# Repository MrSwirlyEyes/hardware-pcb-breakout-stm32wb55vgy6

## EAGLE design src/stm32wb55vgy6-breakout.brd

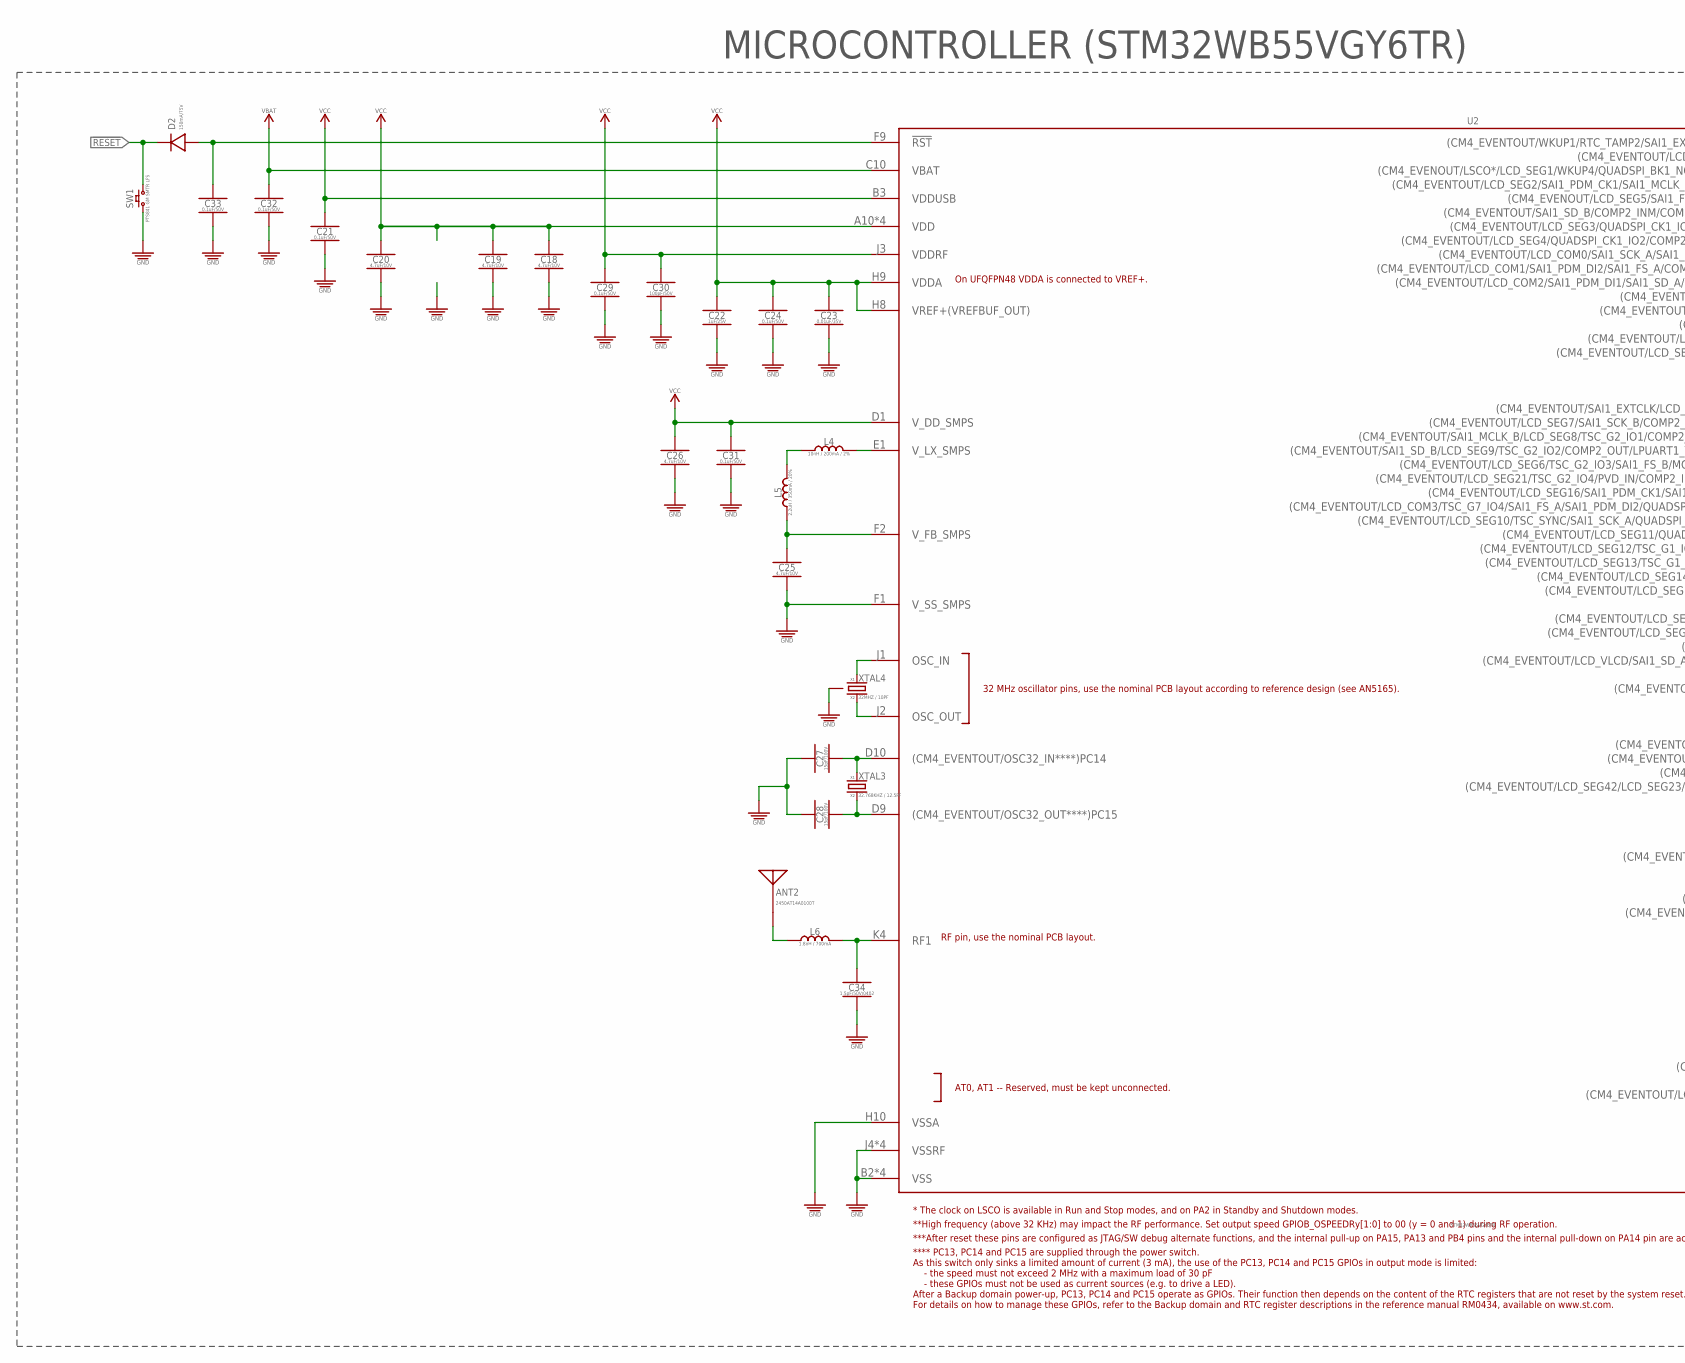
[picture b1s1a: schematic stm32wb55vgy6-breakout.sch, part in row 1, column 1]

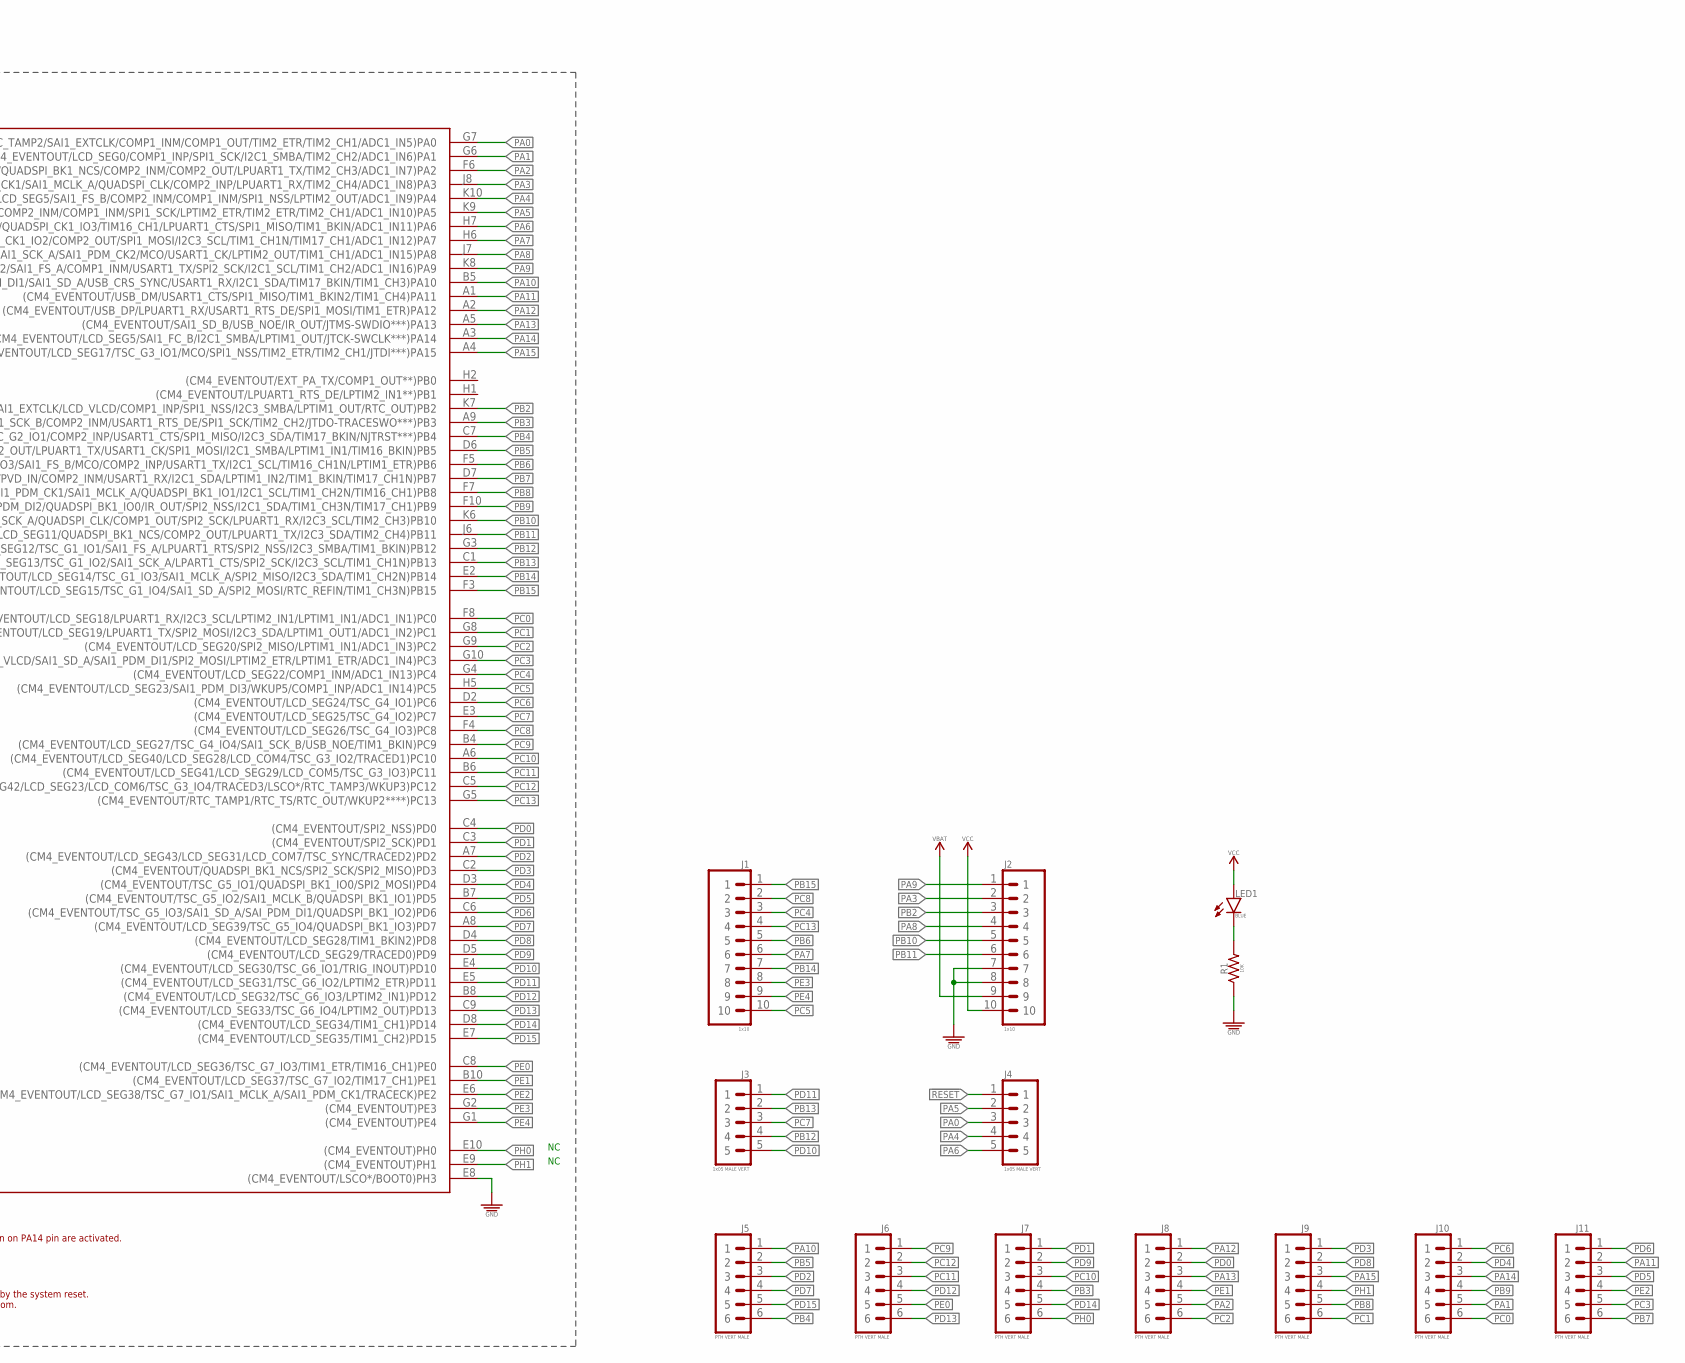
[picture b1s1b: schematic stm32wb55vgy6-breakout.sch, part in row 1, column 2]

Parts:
ANT2: 2450AT14A0100T; RESC1608X40N
C18, C19, C20, C25, C26: 4.7uF/10V; CAPC1005X55_SMD-0402
C21, C24, C29, C31, C32, C33: 0.1uF/50V; CAPC1005X55_SMD-0402
C22: 1uF/25V; CAPC1005X55_SMD-0402
C23: 0.01uF/35V; CAPC1005X55_SMD-0402
C27, C28: 15pF/100V; CAPC1005X55_SMD-0402
C30: 100pF/50V; CAPC1005X55_SMD-0402
C34: 1.5pF/50V/0402; CAPC1005X55_SMD-0402
D2: 150mA/75V; DFN100X60X55-2
J1, J2: 1x10; HDRV10W64P254_1X10_2540X254X838B
J3, J4: 1x05 MALE VERT; HDRV5W64P254_1X5_1270X254X838B
J5, J6, J7, J8, J9, J10, J11: PTH VERT MALE; HDRV6W64P254_1X6_1524X254X838B
L4: 10nH / 200mA / 2%; INDC1005X32N
L5: 2.2uH / 350mA / 20%; INDC1005X32N
L6: 1.8nH / 700mA; INDC1005X32N
LED1: BLUE; LEDC1005X40_LED-0402
R1: 10K; RESC1005X35_SMD-0402
SW1: PTS841 GM SMTR LFS; SW_MOMENTARY_SPST-NO_PTS841-GM-SMTR-LFS
U2: STM32WB55VGY6TR; BGA100N40P10X10_438X440X59N
XTAL3: 32.768KHZ / 12.5PF; OSCCC205X120X55N
XTAL4: 32MHZ / 10PF; OSCCC200X160X59N

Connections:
!RESET!: D2.K, J4.1, SW1.3 (2), SW1.4 (2)
FEED: ANT2.FEED, L6.1
GND: C18.2, C19.2, C20.2, C21.2, C22.2, C23.2, C24.2, C25.2, C26.2, C27.1, C28.1, C29.2, C30.2, C31.2, C32.2, C33.2, C34.2, J2.7, J2.8, R1.1, SW1.1, SW1.2 (1), U2.B2 (VSS), U2.B9 (VSS), U2.E8 ((CM4_EVENTOUT/LSCO*/BOOT0)PH3), U2.F1 (V_SS_SMPS), U2.H10 (VSSA), U2.J4 (VSSRF), U2.J5 (VSS), U2.J9 (VSS), U2.K1 (VSSRF), U2.K2 (VSSRF), U2.K3 (VSSRF), XTAL4.2 (GND), XTAL4.4 (GND)
unnamed: LED1.K, R1.2
unnamed: L4.1, L5.2
unnamed: C25.1, L5.1, U2.F2 (V_FB_SMPS)
unnamed: U2.J1 (OSC_IN), XTAL4.1 (XTAL1)
unnamed: U2.J2 (OSC_OUT), XTAL4.3 (XTAL2)
unnamed: C27.2, U2.D10 ((CM4_EVENTOUT/OSC32_IN****)PC14), XTAL3.X1
unnamed: C28.2, U2.D9 ((CM4_EVENTOUT/OSC32_OUT****)PC15), XTAL3.X2
unnamed: L4.2, U2.E1 (V_LX_SMPS)
unnamed: C33.1, D2.A, U2.F9 (!RST!)
PA0: J4.3, U2.G7 ((CM4_EVENTOUT/WKUP1/RTC_TAMP2/SAI1_EXTC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)
PA1: J10.5, U2.G6 ((CM4_EVENTOUT/LCD_SEG0/COMP1_INP/SPI1_S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)
PA2: J8.5, U2.F6 ((CM4_EVENOUT/LSCO*/LCD_SEG1/WKUP4/QUADS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)
PA3: J2.2, U2.J8 ((CM4_EVENTOUT/LCD_SEG2/SAI1_PDM_CK1/SAI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)
PA4: J4.4, U2.K10 ((CM4_EVENOUT/LCD_SEG5/SAI1_FS_B/COMP2_I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)
PA5: J4.2, U2.K9 ((CM4_EVENTOUT/SAI1_SD_B/COMP2_INM/COMP1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)
PA6: J4.5, U2.H7 ((CM4_EVENTOUT/LCD_SEG3/QUADSPI_CK1_IO3/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)
PA7: J1.6, U2.H6 ((CM4_EVENTOUT/LCD_SEG4/QUADSPI_CK1_IO2/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)
PA8: J2.4, U2.J7 ((CM4_EVENTOUT/LCD_COM0/SAI1_SCK_A/SAI1_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)
PA9: J2.1, U2.K8 ((CM4_EVENTOUT/LCD_COM1/SAI1_PDM_DI2/SAI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)
PA10: J5.1, U2.B5 ((CM4_EVENTOUT/LCD_COM2/SAI1_PDM_DI1/SAI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)
PA11: J11.2, U2.A1 ((CM4_EVENTOUT/USB_DM/USART1_CTS/SPI1_MI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)
PA12: J8.1, U2.A2 ((CM4_EVENTOUT/USB_DP/LPUART1_RX/USART1_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)
PA13: J8.3, U2.A5 ((CM4_EVENTOUT/SAI1_SD_B/USB_NOE/IR_OUT/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)
PA14: J10.3, U2.A3 ((CM4_EVENTOUT/LCD_SEG5/SAI1_FC_B/I2C1_S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)
PA15: J9.3, U2.A4 ((CM4_EVENTOUT/LCD_SEG17/TSC_G3_IO1/MCO/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)
PB2: J2.3, U2.K7 ((CM4_EVENTOUT/SAI1_EXTCLK/LCD_VLCD/COMP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)
PB3: J7.4, U2.A9 ((CM4_EVENTOUT/LCD_SEG7/SAI1_SCK_B/COMP2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)
PB4: J5.6, U2.C7 ((CM4_EVENTOUT/SAI1_MCLK_B/LCD_SEG8/TSC_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)
PB5: J5.2, U2.D6 ((CM4_EVENTOUT/SAI1_SD_B/LCD_SEG9/TSC_G2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)
PB6: J1.5, U2.F5 ((CM4_EVENTOUT/LCD_SEG6/TSC_G2_IO3/SAI1_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)
PB7: J11.6, U2.D7 ((CM4_EVENTOUT/LCD_SEG21/TSC_G2_IO4/PVD_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)
PB8: J9.5, U2.F7 ((CM4_EVENTOUT/LCD_SEG16/SAI1_PDM_CK1/SA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)
PB9: J10.4, U2.F10 ((CM4_EVENTOUT/LCD_COM3/TSC_G7_IO4/SAI1_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)
PB10: J2.5, U2.K6 ((CM4_EVENTOUT/LCD_SEG10/TSC_SYNC/SAI1_S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)
PB11: J2.6, U2.J6 ((CM4_EVENTOUT/LCD_SEG11/QUADSPI_BK1_NCS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)
PB12: J3.4, U2.G3 ((CM4_EVENTOUT/LCD_SEG12/TSC_G1_IO1/SAI1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)
PB13: J3.2, U2.C1 ((CM4_EVENTOUT/LCD_SEG13/TSC_G1_IO2/SAI1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)
PB14: J1.7, U2.E2 ((CM4_EVENTOUT/LCD_SEG14/TSC_G1_IO3/SAI1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)
PB15: J1.1, U2.F3 ((CM4_EVENTOUT/LCD_SEG15/TSC_G1_IO4/SAI1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)
PC0: J10.6, U2.F8 ((CM4_EVENTOUT/LCD_SEG18/LPUART1_RX/I2C3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)
PC1: J9.6, U2.G8 ((CM4_EVENTOUT/LCD_SEG19/LPUART1_TX/SPI2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)
PC2: J8.6, U2.G9 ((CM4_EVENTOUT/LCD_SEG20/SPI2_MISO/LPTIM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)
PC3: J11.5, U2.G10 ((CM4_EVENTOUT/LCD_VLCD/SAI1_SD_A/SAI1_P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)
PC4: J1.3, U2.G4 ((CM4_EVENTOUT/LCD_SEG22/COMP1_INM/ADC1_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)
PC5: J1.10, U2.H5 ((CM4_EVENTOUT/LCD_SEG23/SAI1_PDM_DI3/WK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)
PC6: J10.1, U2.D2 ((CM4_EVENTOUT/LCD_SEG24/TSC_G4_IO1)PC6)
PC7: J3.3, U2.E3 ((CM4_EVENTOUT/LCD_SEG25/TSC_G4_IO2)PC7)
PC8: J1.2, U2.F4 ((CM4_EVENTOUT/LCD_SEG26/TSC_G4_IO3)PC8)
PC9: J6.1, U2.B4 ((CM4_EVENTOUT/LCD_SEG27/TSC_G4_IO4/SAI1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)
PC10: J7.3, U2.A6 ((CM4_EVENTOUT/LCD_SEG40/LCD_SEG28/LCD_C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)
PC11: J6.3, U2.B6 ((CM4_EVENTOUT/LCD_SEG41/LCD_SEG29/LCD_C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)
PC12: J6.2, U2.C5 ((CM4_EVENTOUT/LCD_SEG42/LCD_SEG23/LCD_C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)
PC13: J1.4, U2.G5 ((CM4_EVENTOUT/RTC_TAMP1/RTC_TS/RTC_OUT/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)
PD0: J8.2, U2.C4 ((CM4_EVENTOUT/SPI2_NSS)PD0)
PD1: J7.1, U2.C3 ((CM4_EVENTOUT/SPI2_SCK)PD1)
PD2: J5.3, U2.A7 ((CM4_EVENTOUT/LCD_SEG43/LCD_SEG31/LCD_C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)
PD3: J9.1, U2.C2 ((CM4_EVENTOUT/QUADSPI_BK1_NCS/SPI2_SCK/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)
PD4: J10.2, U2.D3 ((CM4_EVENTOUT/TSC_G5_IO1/QUADSPI_BK1_IO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)
PD5: J11.3, U2.B7 ((CM4_EVENTOUT/TSC_G5_IO2/SAI1_MCLK_B/QU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)
PD6: J11.1, U2.C6 ((CM4_EVENTOUT/TSC_G5_IO3/SAI1_SD_A/SAI_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)
PD7: J5.4, U2.A8 ((CM4_EVENTOUT/LCD_SEG39/TSC_G5_IO4/QUAD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)
PD8: J9.2, U2.D4 ((CM4_EVENTOUT/LCD_SEG28/TIM1_BKIN2)PD8)
PD9: J7.2, U2.D5 ((CM4_EVENTOUT/LCD_SEG29/TRACED0)PD9)
PD10: J3.5, U2.E4 ((CM4_EVENTOUT/LCD_SEG30/TSC_G6_IO1/TRIG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)
PD11: J3.1, U2.E5 ((CM4_EVENTOUT/LCD_SEG31/TSC_G6_IO2/LPTI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)
PD12: J6.4, U2.B8 ((CM4_EVENTOUT/LCD_SEG32/TSC_G6_IO3/LPTI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)
PD13: J6.6, U2.C9 ((CM4_EVENTOUT/LCD_SEG33/TSC_G6_IO4/LPTI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)
PD14: J7.5, U2.D8 ((CM4_EVENTOUT/LCD_SEG34/TIM1_CH1)PD14)
PD15: J5.5, U2.E7 ((CM4_EVENTOUT/LCD_SEG35/TIM1_CH2)PD15)
PE0: J6.5, U2.C8 ((CM4_EVENTOUT/LCD_SEG36/TSC_G7_IO3/TIM1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)
PE1: J8.4, U2.B10 ((CM4_EVENTOUT/LCD_SEG37/TSC_G7_IO2/TIM1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)
PE2: J11.4, U2.E6 ((CM4_EVENTOUT/LCD_SEG38/TSC_G7_IO1/SAI1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)
PE3: J1.8, U2.G2 ((CM4_EVENTOUT)PE3)
PE4: J1.9, U2.G1 ((CM4_EVENTOUT)PE4)
PH0: J7.6, U2.E10 ((CM4_EVENTOUT)PH0)
PH1: J9.4, U2.E9 ((CM4_EVENTOUT)PH1)
RF: C34.1, L6.2, U2.K4 (RF1)
VBAT: C32.1, J2.9, U2.C10 (VBAT)
VCC: C18.1, C19.1, C20.1, C21.1, C22.1, C23.1, C24.1, C26.1, C29.1, C30.1, C31.1, J2.10, LED1.A, U2.A10 (VDD), U2.B1 (VDD), U2.B3 (VDDUSB), U2.D1 (V_DD_SMPS), U2.H8 (VREF+(VREFBUF_OUT)), U2.H9 (VDDA), U2.J3 (VDDRF), U2.J10 (VDD), U2.K5 (VDD)

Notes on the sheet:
MICROCONTROLLER (STM32WB55VGY6TR)

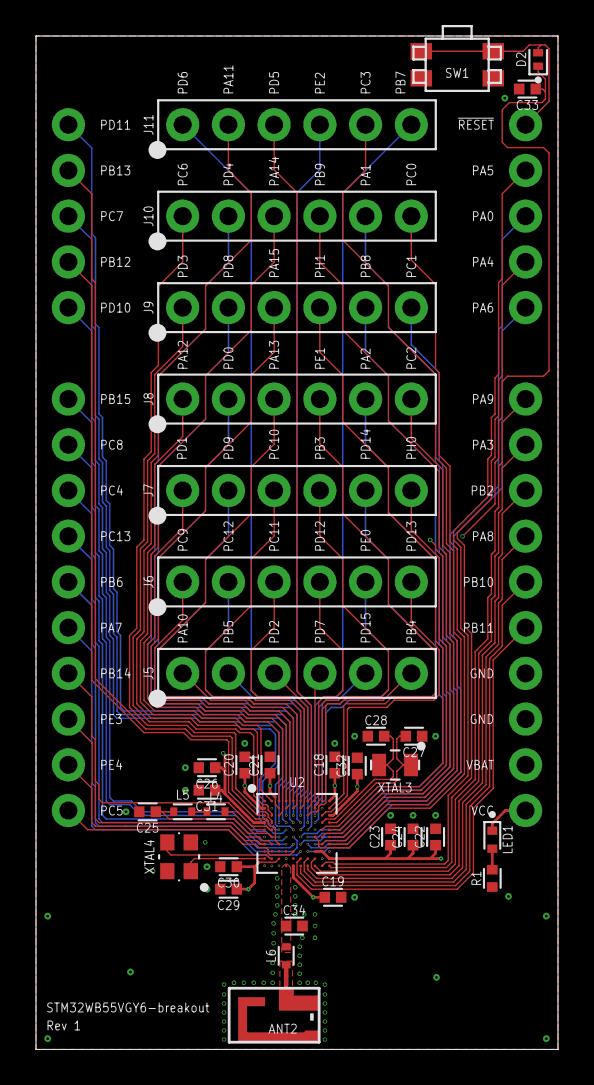
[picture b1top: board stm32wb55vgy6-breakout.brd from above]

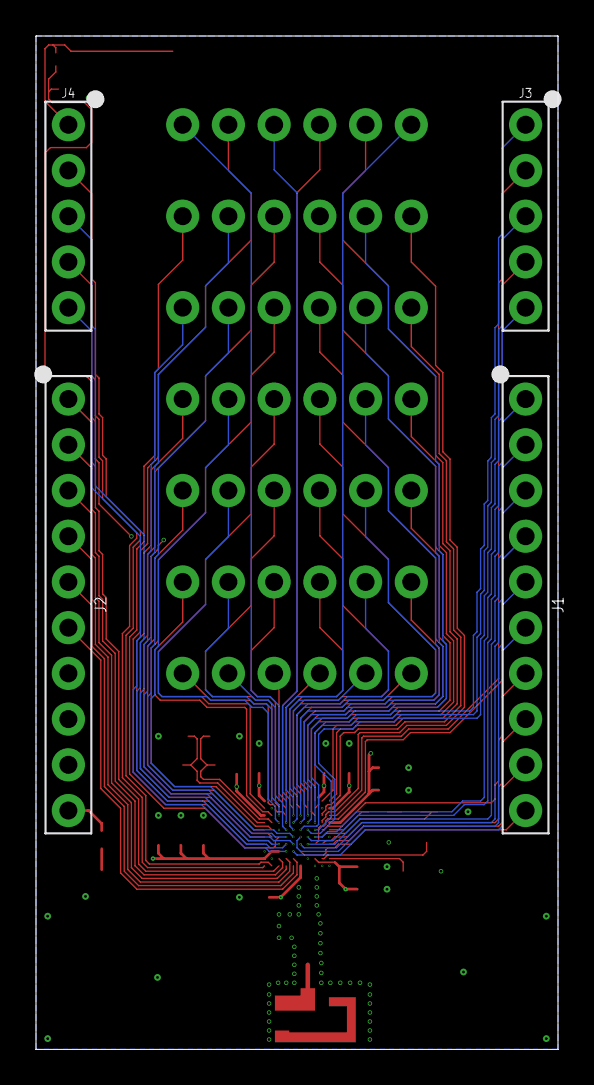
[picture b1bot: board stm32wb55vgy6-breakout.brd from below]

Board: 4 copper layers, 29.0 x 56.3 mm, 39 parts (4 on the bottom side), 82 nets.

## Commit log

2021-01-12 [Rev 1] - Initialize repo.
2021-01-17 [Rev 1] - Adjusted antenna microstrip width to more closely approximate a 50 ohm impedence. Added LED power indicator to VCC. Moved antenna circuitry to center of the board instead of the corner.
2021-08-11 Update CAM files.
